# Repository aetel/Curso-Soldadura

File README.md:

# Curso-Soldadura
Curso Iniciación Soldadura

PCB y Prensentación para un curso de iniciación a la soldadura

Lista de componentes:

| Cantidad | Componente | Valor | Nombre |
| ------------- | ------------- | ------------- | ------------- |
|2x|Leds 5mm|Color a elegir|LED1, LED2 |
|2x|Resistencia 1/4w|330 Ω|R1, R2|
|2x|Resistencia 1/4w|33k Ω|R3, R4|
|2x|Transistor NPN|BC547|T1, T2|
|2x|Condensador Electrolítico|10uF|C1, C2|
|1x|Bornera para cable|(Opcional)|9V|
|1x|Porta Pilas 9V|9V|9V|
|1x|Pila|9V|Batería|

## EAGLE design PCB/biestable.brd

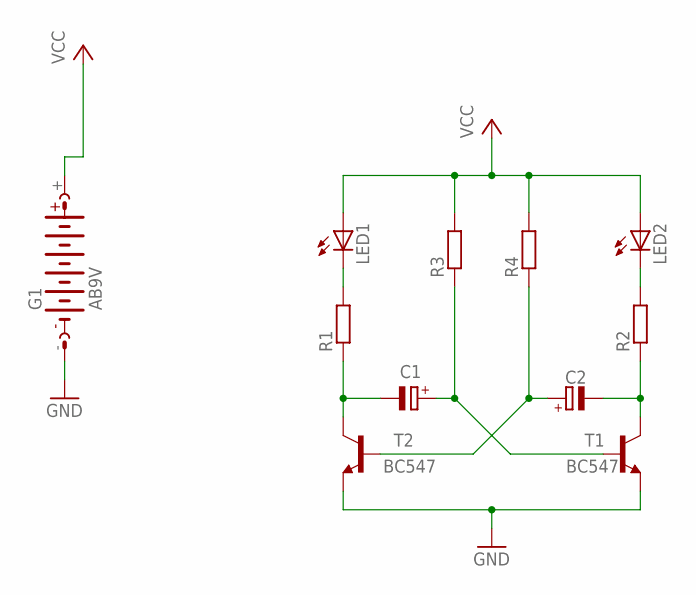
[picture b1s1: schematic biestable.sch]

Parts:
C1, C2: CPOL-EUE1.8-4; E1,8-4
G1: AB9V
LED1, LED2: LED5MM
R1, R2, R3, R4: R0207/10; 0207/10
T1, T2: BC547; TO92

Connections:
GND: G1.-, T1.1 (E), T2.1 (E)
unnamed: LED1.K (C), R1.2
unnamed: LED2.K (C), R2.2
unnamed: C1.-, R1.1, T2.3 (C)
unnamed: C1.+, R3.1, T1.2 (B)
unnamed: C2.+, R4.1, T2.2 (B)
unnamed: C2.-, R2.1, T1.3 (C)
VCC: G1.+, LED1.A, LED2.A, R3.2, R4.2

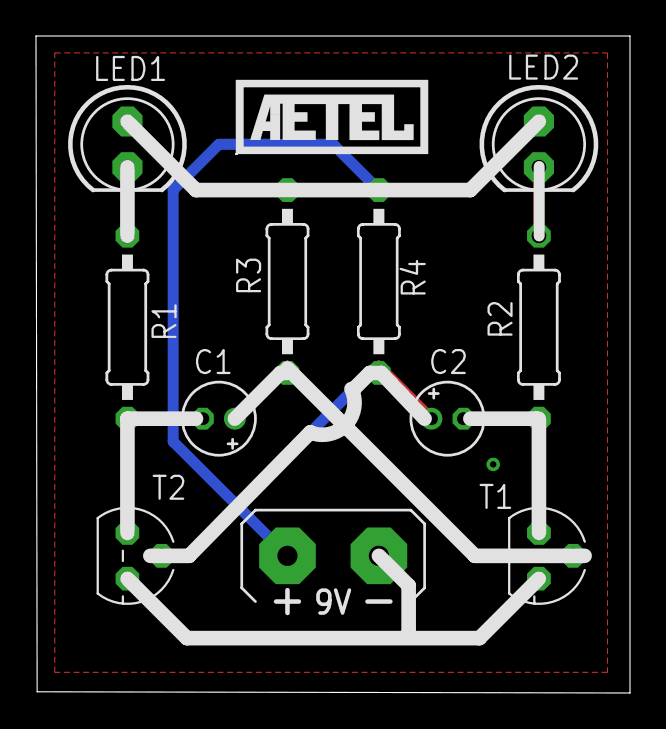
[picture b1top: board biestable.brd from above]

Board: 2 copper layers, 33.0 x 36.5 mm, 11 parts (0 on the bottom side), 8 nets.
